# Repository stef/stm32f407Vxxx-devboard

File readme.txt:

cc0 licensed breakout board for stm32f407Vxxx

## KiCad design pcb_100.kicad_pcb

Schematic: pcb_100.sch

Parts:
B1, B2: SWITCH_4PIN
C1, C2, C23, C24: 2.2u
C3, C20: 22p
C4, C8, C9, C10, C11, C12, C13, C14, C15, C16, C17, C18, C19, C22, C25, C27, C29: 100n
C21: 4.7u
C26, C28: 1u
D1: SML-211UTT86
D2: SML-211YTT86
JP1: JUMPER3
L1: 30@100MHz
L2: 22@100MHz
P1, P2, P3: DIL32
P6: CONN_3
P7: USB-MINI-B
R1, R2: 1k
U1: STM32F40XVX
U6: LP38691
X1: CRYSTAL

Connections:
+3.3V: C2.1, C8.2, C9.2, C10.2, C11.2, C12.2, C13.2, C14.2, C15.2, C16.2, C17.2, C18.2, C19.2, C21.2, C22.1, L2.1, P3.19, P3.20, P3.23, P3.24, P3.27, R1.1, U1.6, U1.11, U1.19, U1.28, U1.50, U1.75, U1.100, U6.1 (Vout)
+5V: C1.1, JP1.2, P3.21, P3.22, U6.3 (Vin)
/3V3_adc: C25.1, C26.1, C27.1, C28.1, L2.2, U1.21, U1.22
/boot0: B2.1, B2.2, C4.2, U1.94
/ext_5v: JP1.3, P6.1
/nrst: B1.1, B1.2, C29.2, P3.31, U1.14
/osc_in: C3.1, U1.12, X1.2
/osc_out: C20.1, U1.13, X1.1
/pa0: P1.1, U1.23
/pa1: P1.2, U1.24
/pa2: P1.3, U1.25
/pa3: P1.4, U1.26
/pa4: P1.5, U1.29
/pa5: P1.6, U1.30
/pa6: P1.7, U1.31
/pa7: P1.8, U1.32
/pa8: P1.9, U1.67
/pa9: P1.10, U1.68
/pa15: P1.16, U1.77
/pb0: P1.17, U1.35
/pb1: P1.18, U1.36
/pb2: P1.19, U1.37
/pb4: P1.21, U1.90
/pb5: P1.22, U1.91
/pb6: P1.23, U1.92
/pb7: P1.24, U1.93
/pb8: P1.25, U1.95
/pb9: P1.26, U1.96
/pb10: P1.27, U1.47
/pb11: P1.28, U1.48
/pb12: P1.29, U1.51
/pb13: P1.30, U1.52
/pb14: P1.31, U1.53
/pb15: P1.32, U1.54
/pc0: P2.1, U1.15
/pc2: P2.3, U1.17
/pc3: P2.4, U1.18
/pc4: P2.5, U1.33
/pc5: P2.6, U1.34
/pc6: P2.7, U1.63
/pc7: P2.8, U1.64
/pc15: P2.16, U1.9
/pd0: P2.17, U1.81
/pd1: P2.18, U1.82
/pd2: P2.19, U1.83
/pd3: P2.20, U1.84
/pd4: P2.21, U1.85
/pd5: P2.22, U1.86
/pd6: P2.23, U1.87
/pd7: P2.24, U1.88
/pd8: P2.25, U1.55
/pd9: P2.26, U1.56
/pd10: P2.27, U1.57
/pd11: P2.28, U1.58
/pd12: P2.29, U1.59
/pd13: P2.30, U1.60
/pd14: P2.31, U1.61
/pd15: P2.32, U1.62
/pe0: P3.1, U1.97
/pe1: P3.2, U1.98
/pe2: P3.3, U1.1
/pe3: P3.4, U1.2
/pe4: P3.5, U1.3
/pe5: P3.6, U1.4
/pe6: P3.7, U1.5
/pe7: P3.8, U1.38
/pe8: P3.9, U1.39
/pe9: P3.10, U1.40
/pe10: P3.11, U1.41
/pe11: P3.12, U1.42
/pe12: P3.13, U1.43
/pe13: P3.14, U1.44
/pe14: P3.15, U1.45
/pe15: P3.16, U1.46
/sd_cd: P2.14, U1.7
/sd_clk: P2.13, U1.80
/sd_d0: P2.9, U1.65
/sd_d1: P2.10, U1.66
/sd_d2: P2.11, U1.78
/sd_d3: P2.12, U1.79
/sd_wp: P2.15, U1.8
/swclk: P1.15, P3.28, U1.76
/swdio: P1.14, P3.30, U1.72
/swo: P1.20, P3.32, U1.89
/usb_5v: JP1.1, P7.1 (VBUS)
/usb_dm: P1.12, P7.2 (D-), U1.70
/usb_dp: P1.13, P7.3 (D+), U1.71
/usb_id: P1.11, P7.4 (ID), U1.69
/user_led: P2.2, R2.1, U1.16
/vcap_1: C23.1, U1.49
/vcap_2: C24.1, U1.73
GND: B1.3, B1.4, B2.3, B2.4, C1.2, C2.2, C3.2, C4.1, C8.1, C9.1, C10.1, C11.1, C12.1, C13.1, C14.1, C15.1, C16.1, C17.1, C18.1, C19.1, C20.2, C21.1, C22.2, C23.2, C24.2, C25.2, C26.2, C27.2, C28.2, C29.1, D1.2 (K), D2.2 (K), L1.1, P3.17, P3.18, P3.25, P3.26, P3.29, P6.3, P7.5 (GND), U1.10, U1.20, U1.27, U1.74, U1.99, U6.2 (GND)
unnamed: L1.2, P7.6 (SHELL1), P7.7 (SHELL2), P7.8 (SHELL3), P7.9 (SHELL4)
unnamed: D1.1 (A), R1.2
unnamed: D2.1 (A), R2.2

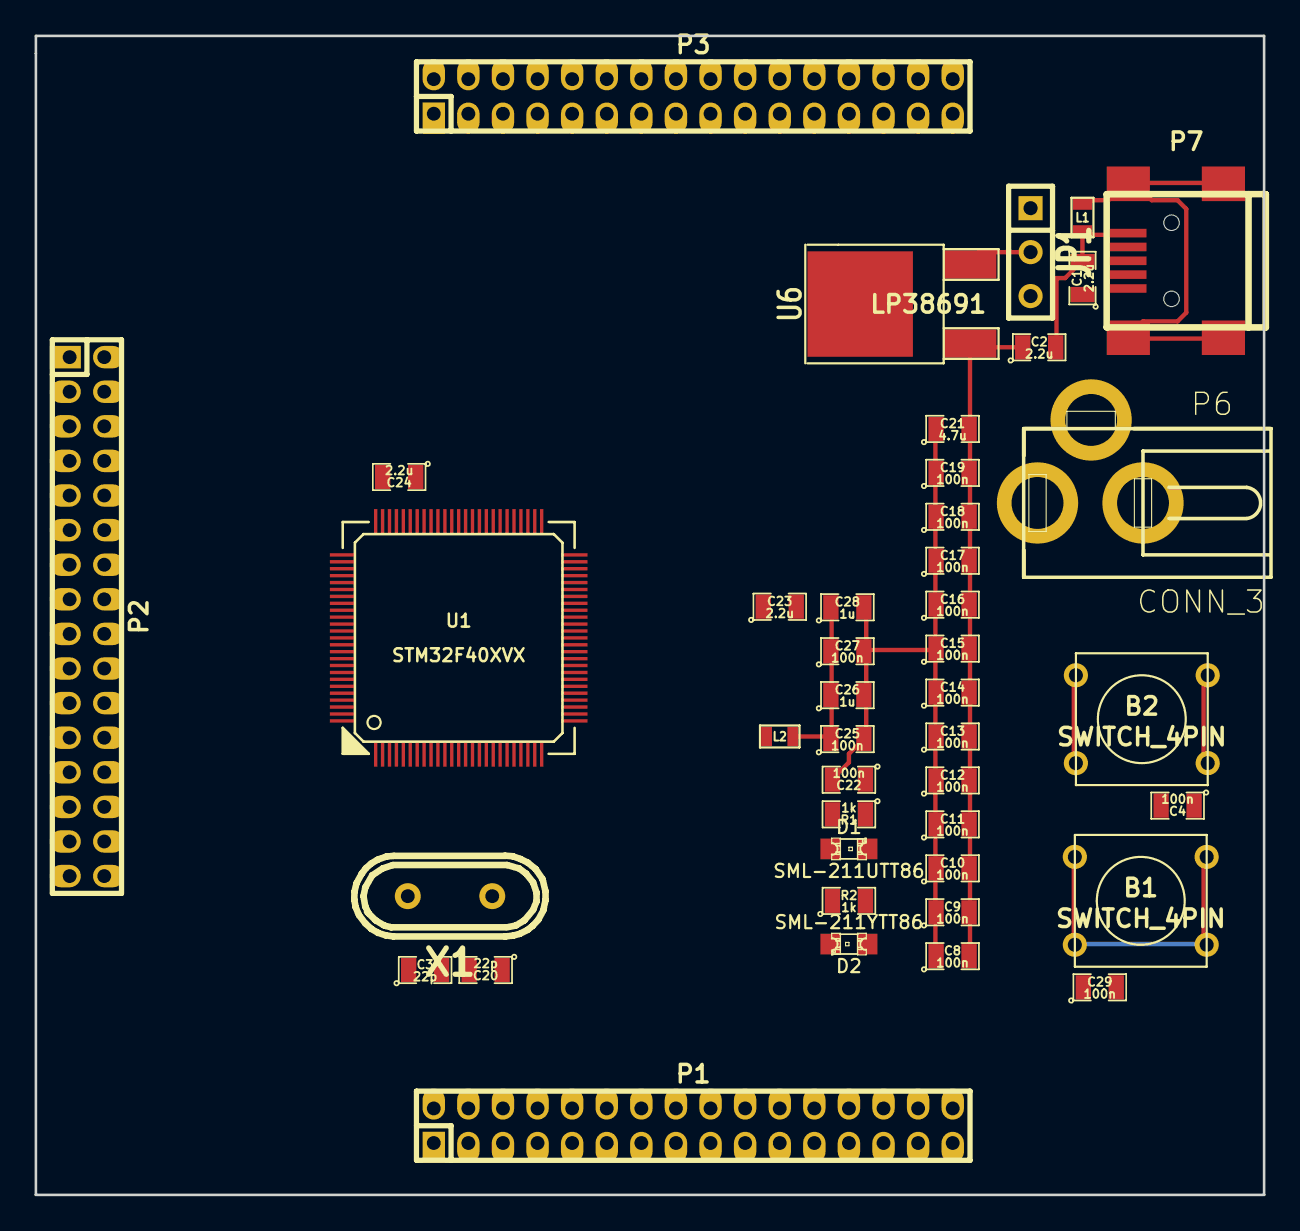
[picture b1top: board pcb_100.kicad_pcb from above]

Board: 2 copper layers, 71.0 x 67.0 mm, 43 parts (0 on the bottom side), 95 nets.

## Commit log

2014-02-21 [enh] initial commit
